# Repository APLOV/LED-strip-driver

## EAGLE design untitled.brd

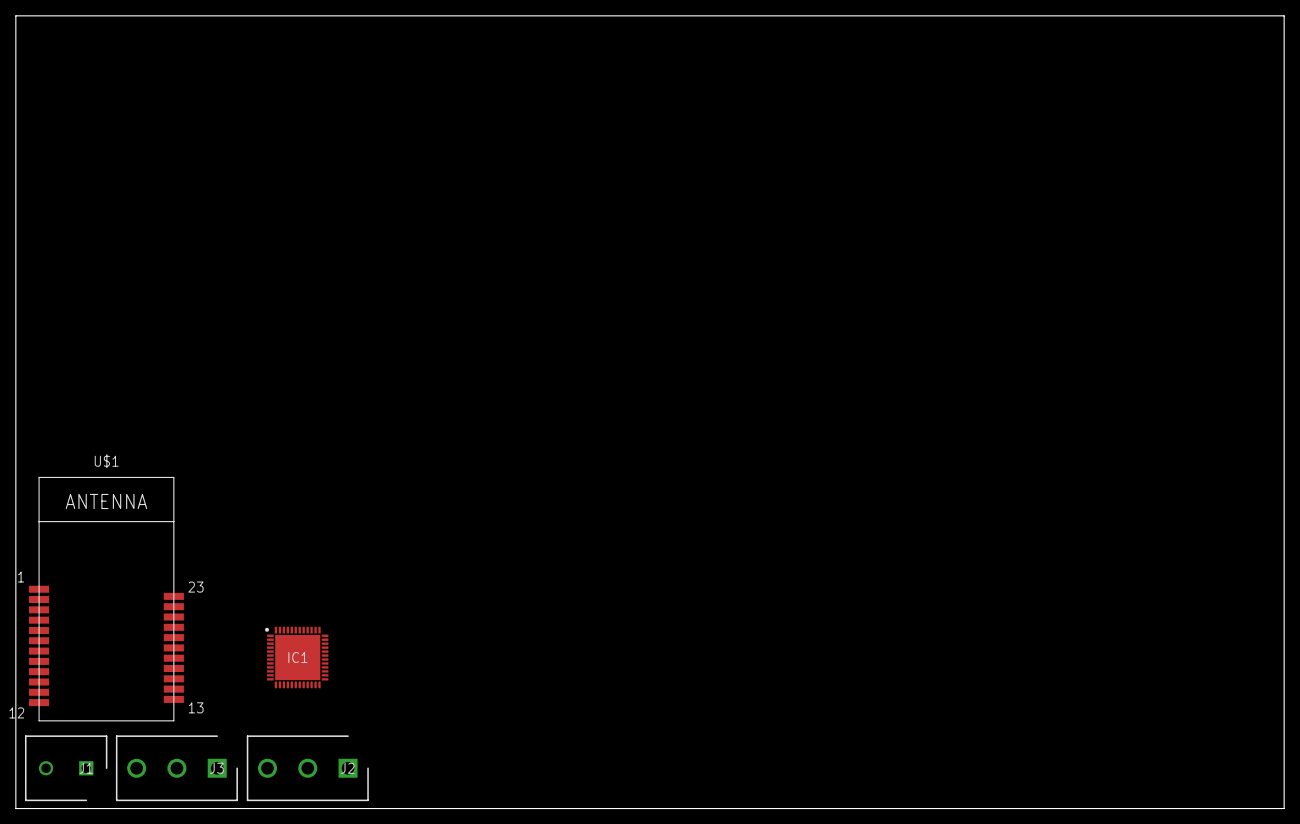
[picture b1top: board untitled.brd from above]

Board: 2 copper layers, 160.0 x 100.0 mm, 5 parts (0 on the bottom side), 3 nets, no tracks yet.

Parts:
IC1: STM32F411CEU6; QFN50P700X700X60-49N
J1: CTB0508_2; SHDR2W100P0X508_1X2_1020X810X1
J2, J3: CTB0508_3; SHDR3W100P0X508_1X3_1520X810X1
U$1: WIRELESS-BLUETOOTH-XS3868

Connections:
1: J2.1, J3.1
2: J2.2, J3.2
3: J2.3, J3.3

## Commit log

2019-09-17 init

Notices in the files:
parts and their libraries:
XS3868OVC3860: Released under the Creative Commons Attribution 4.0 International License: http://creativecommons.org/licenses/by/4.0
